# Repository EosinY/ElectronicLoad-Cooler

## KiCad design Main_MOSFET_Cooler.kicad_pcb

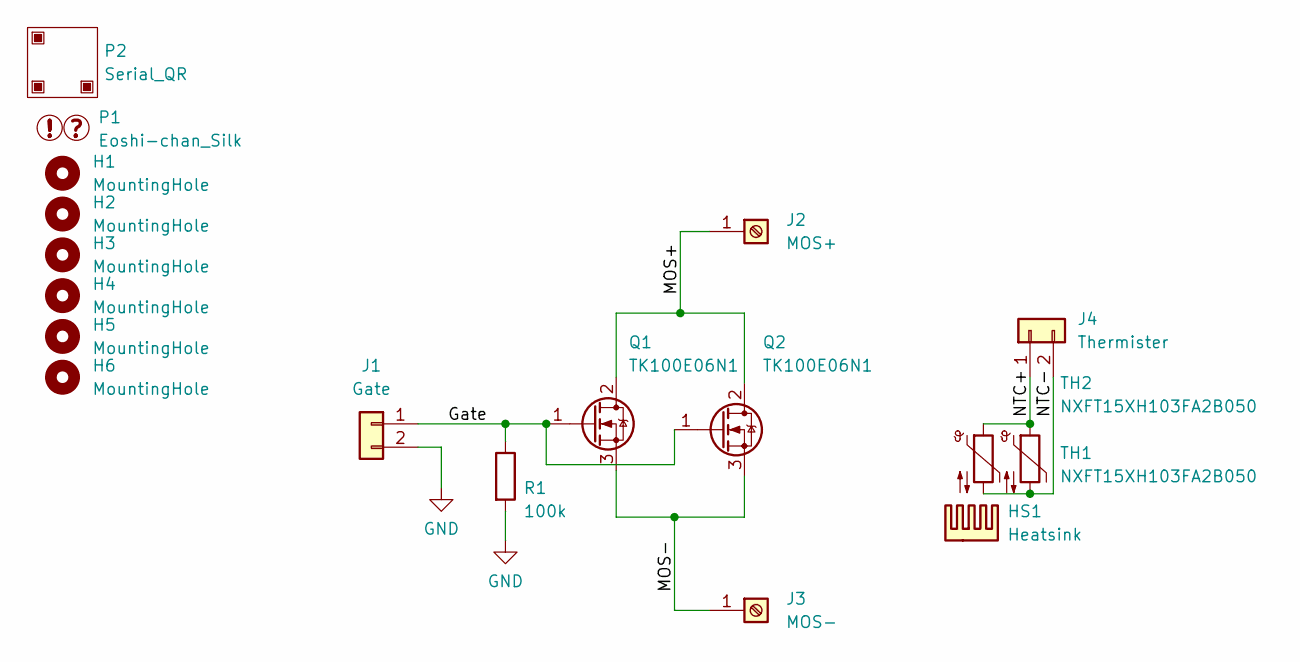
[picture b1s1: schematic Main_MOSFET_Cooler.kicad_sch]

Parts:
H1, H2, H3, H4, H5, H6: MountingHole; MountingHole_3.2mm_M3
HS1: Heatsink; LGA1700_Cooler
J1: Gate; JST_XH_S2B-XH-A_1x02_P2.50mm_Horizontal
J2: MOS+; ScrewTerminal_01x01_PCB-20
J3: MOS-; ScrewTerminal_01x01_PCB-20
J4: Thermister; JST_XH_B2B-XH-A_1x02_P2.50mm_Vertical
P1: Eoshi-chan_Silk; Eoshi-chan-v2_20x20
P2: Serial_QR; Serial_QR_10x10
Q1, Q2: TK100E06N1; TO-220-3_Horizontal_TabDown
R1: 100k; R_0603_1608Metric
TH1: NXFT15XH103FA2B050; C_Disc_D3.0mm_W1.6mm_P2.50mm
TH2: NXFT15XH103FA2B050; R_0402_1005Metric

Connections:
/Gate: J1.1, Q1.1 (G), Q2.1 (G), R1.1
/MOS+: J2.1, Q1.2 (D), Q2.2 (D)
/MOS-: J3.1, Q1.3 (S), Q2.3 (S)
/NTC+: J4.1, TH1.1, TH2.1
/NTC-: J4.2, TH1.2, TH2.2
GND: J1.2, R1.2

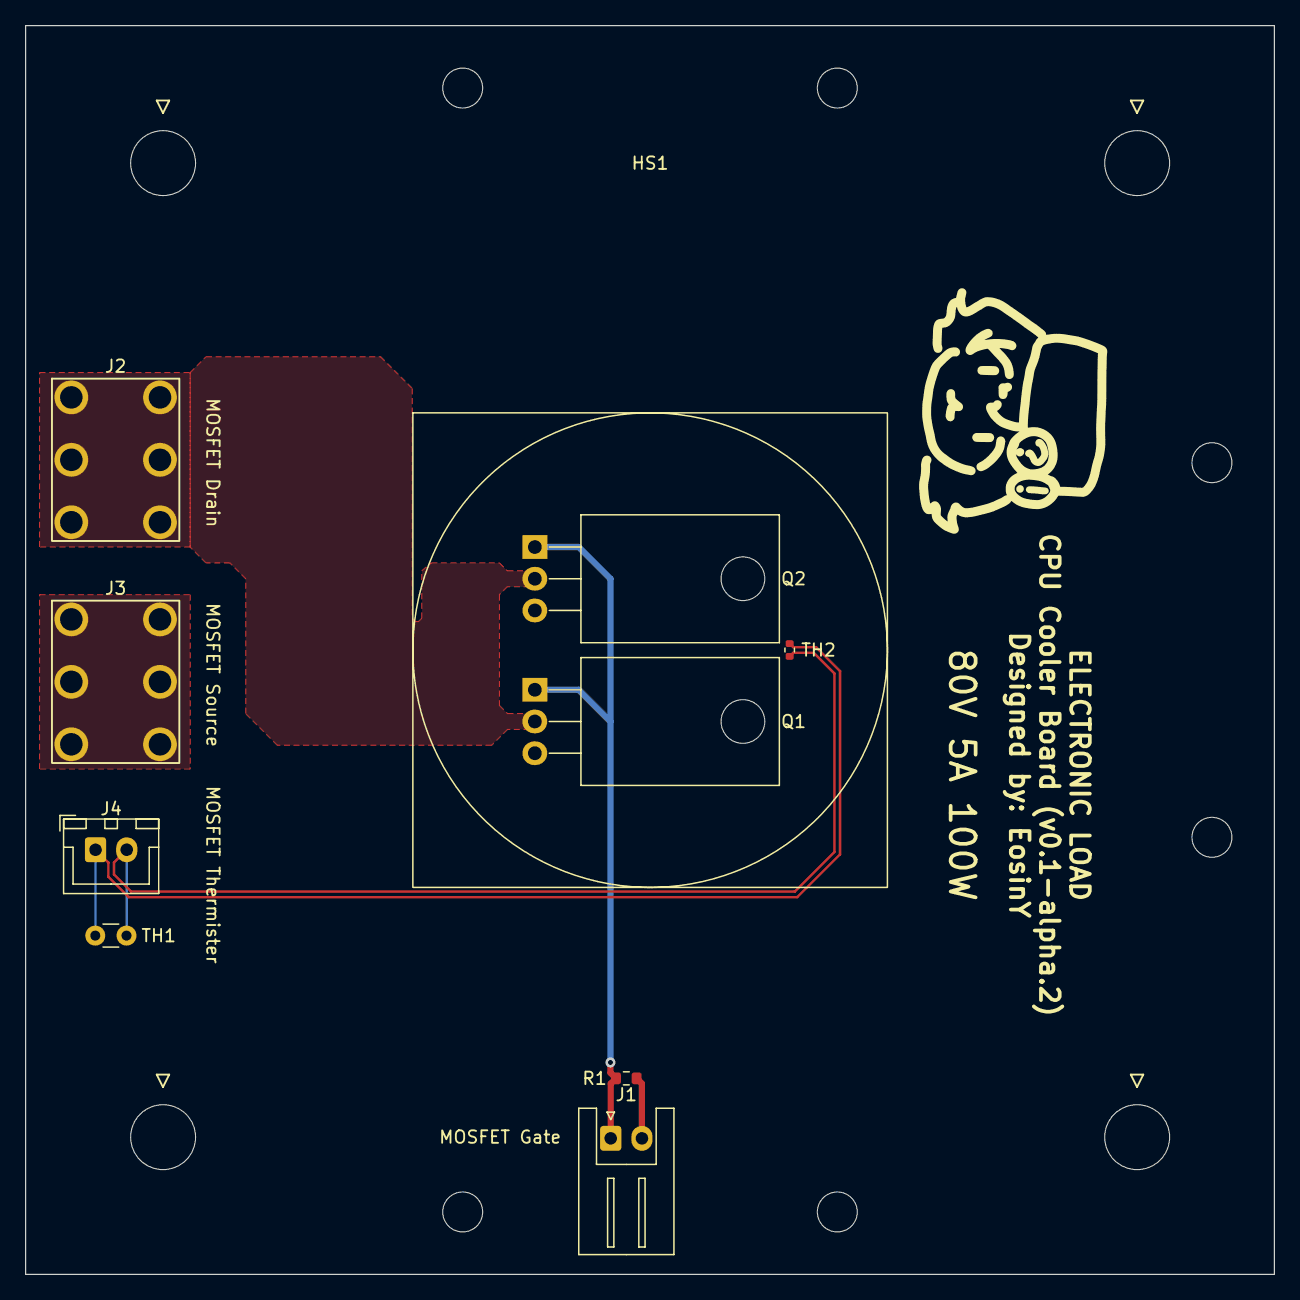
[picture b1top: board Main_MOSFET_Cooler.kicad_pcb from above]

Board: 2 copper layers, 100.0 x 100.0 mm, 18 parts (1 on the bottom side), 6 nets.

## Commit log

2025-03-13 First
2025-04-23 before mirror
2025-05-29 added 5.45mm pitch version
